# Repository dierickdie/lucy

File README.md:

# Lucy

An 4x12 ortho plus macro column keyboard.

**USE AT YOUR OWN RISK!!!** I am not responsible for any dumb things you do. Like fry your computer, break anything, etc.

## FAQ:
#### Does it have MIT/2x2u/etc.? 
No. Grid for life

#### Does it have backlighting?
No

#### Does it have RGB?
No

#### Does it have hotswap?
~No~ Fine

#### Does it have Alps support?
No

#### Choc support?
No

#### Encoder?
Not anymore; they're are a dead meme

#### Flex cuts?
See response to encoder

#### Will you add any of these?
No

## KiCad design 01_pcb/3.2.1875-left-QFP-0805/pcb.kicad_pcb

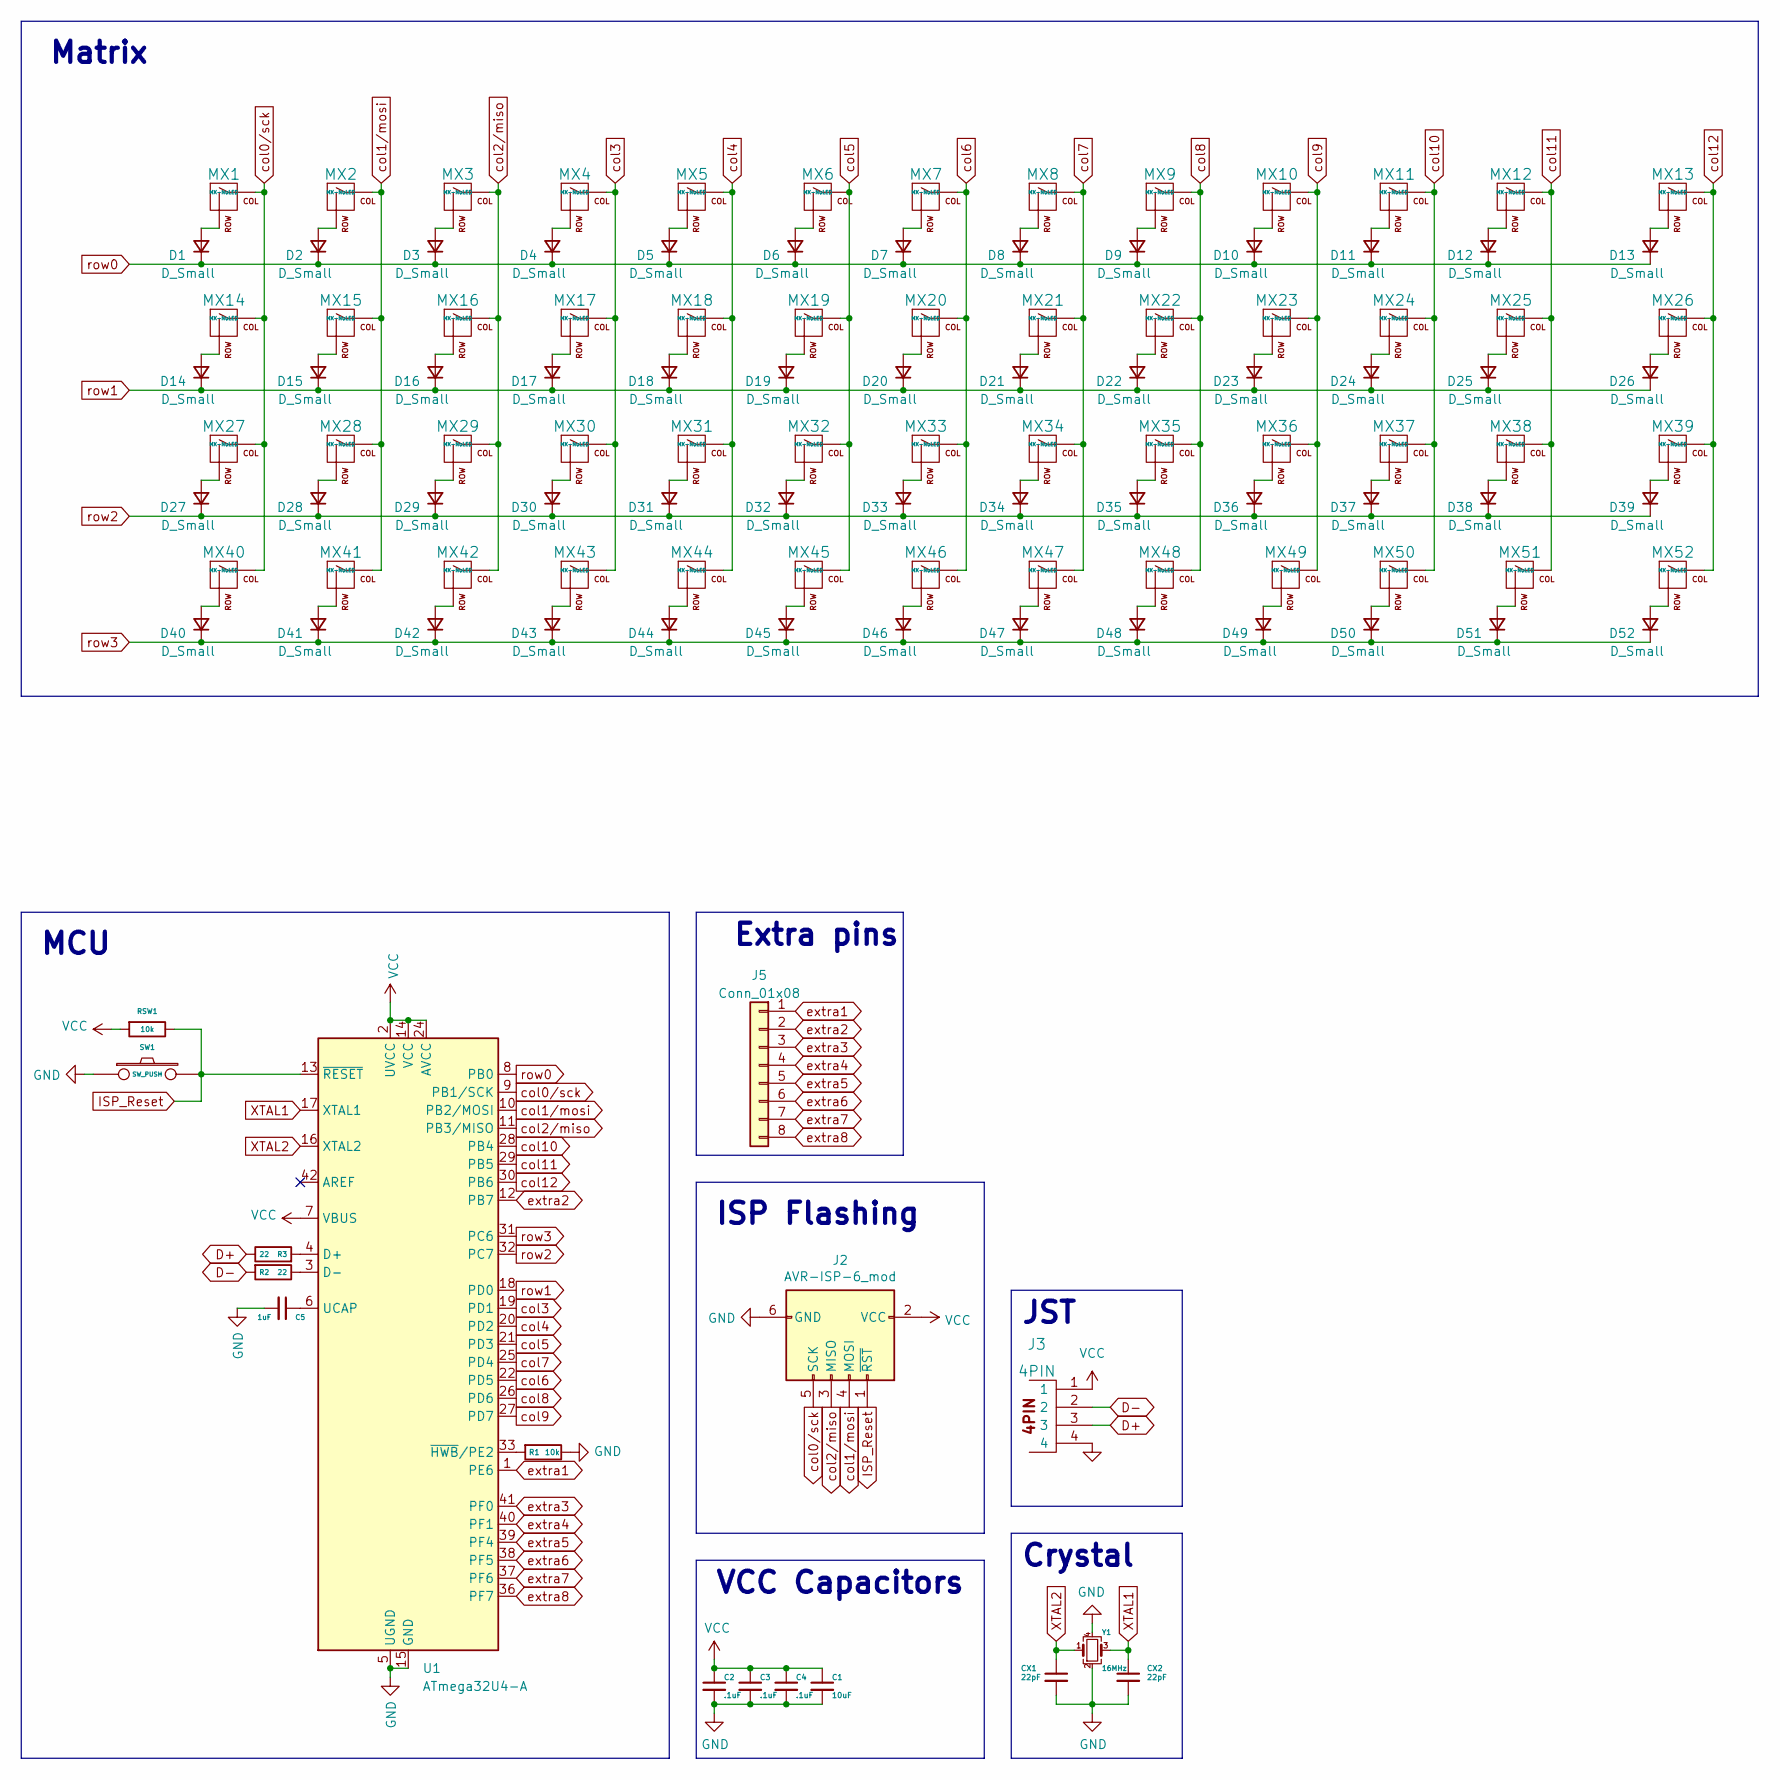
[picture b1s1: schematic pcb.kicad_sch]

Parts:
C1: 10uF; C_0805_2012Metric
C2, C3, C4: .1uF; C_0805_2012Metric
C5: 1uF; C_0805_2012Metric
CX1, CX2: 22pF; C_0805_2012Metric
D1, D2, D3, D4, D5, D6, D7, D8, D9, D10, D11, D12, D13, D14, D15, D16, D17, D18, D19, D20, D21, D22, D23, D24, D25, D26, D27, D28, D29, D30, D31, D32, D33, D34, D35, D36, D37, D38, D39, D40, D41, D42, D43, D44, D45, D46, D47, D48, D49, D50, D51, D52: D_Small; D_SOD-123
J2: AVR-ISP-6_mod; PinHeader_1x6_P2.54mm_Vertical
J3: 4PIN; JST_SH_SM04B-SRSS-TB_1x04-1MP_P1.00mm_Horizontal
J5: Conn_01x08; PinSocket_1x08_P2.54mm_Vertical
MX1, MX2, MX3, MX4, MX5, MX6, MX7, MX8, MX9, MX10, MX11, MX12, MX13, MX14, MX15, MX16, MX17, MX18, MX19, MX20, MX21, MX22, MX23, MX24, MX25, MX26, MX27, MX28, MX29, MX30, MX31, MX32, MX33, MX34, MX35, MX36, MX37, MX38, MX39, MX40, MX41, MX42, MX43, MX44, MX45, MX46, MX47, MX48, MX49, MX50, MX51, MX52: MX-NoLED; SW_MX_HS_S_1u
R1: 10k; R_0805_2012Metric
R2, R3: 22; R_0805_2012Metric
RSW1: 10k; R_0805_2012Metric
SW1: SW_PUSH; SKQG-1155865
U1: ATmega32U4-A; TQFP-44_10x10mm_P0.8mm
Y1: 16MHz; Crystal_SMD_3225-4Pin_3.2x2.5mm

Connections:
D+: J3.3, R3.1
D-: J3.2, R2.2
GND: C1.2, C2.2, C3.2, C4.2, C5.2, CX1.2, CX2.2, J2.6 (GND), J3.4, R1.1, SW1.1, U1.5 (UGND), U1.15 (GND), U1.23 (GND), U1.35 (GND), U1.43 (GND), Y1.2, Y1.4
ISP_Reset: J2.1 (~RST), RSW1.1, SW1.2, U1.13 (~RESET)
unnamed: D1.2 (A), MX1.2 (ROW)
unnamed: D2.2 (A), MX2.2 (ROW)
unnamed: D3.2 (A), MX3.2 (ROW)
unnamed: D4.2 (A), MX4.2 (ROW)
unnamed: D5.2 (A), MX5.2 (ROW)
unnamed: D6.2 (A), MX6.2 (ROW)
unnamed: D7.2 (A), MX7.2 (ROW)
unnamed: D8.2 (A), MX8.2 (ROW)
unnamed: D9.2 (A), MX9.2 (ROW)
unnamed: D10.2 (A), MX10.2 (ROW)
unnamed: D11.2 (A), MX11.2 (ROW)
unnamed: D12.2 (A), MX12.2 (ROW)
unnamed: D13.2 (A), MX13.2 (ROW)
unnamed: D14.2 (A), MX14.2 (ROW)
unnamed: D15.2 (A), MX15.2 (ROW)
unnamed: D16.2 (A), MX16.2 (ROW)
unnamed: D17.2 (A), MX17.2 (ROW)
unnamed: D18.2 (A), MX18.2 (ROW)
unnamed: D19.2 (A), MX19.2 (ROW)
unnamed: D20.2 (A), MX20.2 (ROW)
unnamed: D21.2 (A), MX21.2 (ROW)
unnamed: D22.2 (A), MX22.2 (ROW)
unnamed: D23.2 (A), MX23.2 (ROW)
unnamed: D24.2 (A), MX24.2 (ROW)
unnamed: D25.2 (A), MX25.2 (ROW)
unnamed: D26.2 (A), MX26.2 (ROW)
unnamed: D27.2 (A), MX27.2 (ROW)
unnamed: D28.2 (A), MX28.2 (ROW)
unnamed: D29.2 (A), MX29.2 (ROW)
unnamed: D30.2 (A), MX30.2 (ROW)
unnamed: D31.2 (A), MX31.2 (ROW)
unnamed: D32.2 (A), MX32.2 (ROW)
unnamed: D33.2 (A), MX33.2 (ROW)
unnamed: D34.2 (A), MX34.2 (ROW)
unnamed: D35.2 (A), MX35.2 (ROW)
unnamed: D36.2 (A), MX36.2 (ROW)
unnamed: D37.2 (A), MX37.2 (ROW)
unnamed: D38.2 (A), MX38.2 (ROW)
unnamed: D39.2 (A), MX39.2 (ROW)
unnamed: D40.2 (A), MX40.2 (ROW)
unnamed: D41.2 (A), MX41.2 (ROW)
unnamed: D42.2 (A), MX42.2 (ROW)
unnamed: D43.2 (A), MX43.2 (ROW)
unnamed: D44.2 (A), MX44.2 (ROW)
unnamed: D45.2 (A), MX45.2 (ROW)
unnamed: D46.2 (A), MX46.2 (ROW)
unnamed: D47.2 (A), MX47.2 (ROW)
unnamed: D48.2 (A), MX48.2 (ROW)
unnamed: D49.2 (A), MX49.2 (ROW)
unnamed: D50.2 (A), MX50.2 (ROW)
unnamed: D51.2 (A), MX51.2 (ROW)
unnamed: D52.2 (A), MX52.2 (ROW)
unnamed: R3.2, U1.4 (D+)
unnamed: R2.1, U1.3 (D-)
unnamed: C5.1, U1.6 (UCAP)
unnamed: R1.2, U1.33 (~HWB/PE2)
VCC: C1.1, C2.1, C3.1, C4.1, J2.2 (VCC), J3.1, RSW1.2, U1.2 (UVCC), U1.7 (VBUS), U1.14 (VCC), U1.24 (AVCC), U1.34 (VCC), U1.44 (AVCC)
XTAL1: CX2.1, U1.17 (XTAL1), Y1.3
XTAL2: CX1.1, U1.16 (XTAL2), Y1.1
col0/sck: J2.5 (SCK), MX1.1 (COL), MX14.1 (COL), MX27.1 (COL), MX40.1 (COL), U1.9 (PB1/SCK)
col1/mosi: J2.4 (MOSI), MX2.1 (COL), MX15.1 (COL), MX28.1 (COL), MX41.1 (COL), U1.10 (PB2/MOSI)
col2/miso: J2.3 (MISO), MX3.1 (COL), MX16.1 (COL), MX29.1 (COL), MX42.1 (COL), U1.11 (PB3/MISO)
col3: MX4.1 (COL), MX17.1 (COL), MX30.1 (COL), MX43.1 (COL), U1.19 (PD1)
col4: MX5.1 (COL), MX18.1 (COL), MX31.1 (COL), MX44.1 (COL), U1.20 (PD2)
col5: MX6.1 (COL), MX19.1 (COL), MX32.1 (COL), MX45.1 (COL), U1.21 (PD3)
col6: MX7.1 (COL), MX20.1 (COL), MX33.1 (COL), MX46.1 (COL), U1.22 (PD5)
col7: MX8.1 (COL), MX21.1 (COL), MX34.1 (COL), MX47.1 (COL), U1.25 (PD4)
col8: MX9.1 (COL), MX22.1 (COL), MX35.1 (COL), MX48.1 (COL), U1.26 (PD6)
col9: MX10.1 (COL), MX23.1 (COL), MX36.1 (COL), MX49.1 (COL), U1.27 (PD7)
col10: MX11.1 (COL), MX24.1 (COL), MX37.1 (COL), MX50.1 (COL), U1.28 (PB4)
col11: MX12.1 (COL), MX25.1 (COL), MX38.1 (COL), MX51.1 (COL), U1.29 (PB5)
col12: MX13.1 (COL), MX26.1 (COL), MX39.1 (COL), MX52.1 (COL), U1.30 (PB6)
extra1: J5.1, U1.1 (PE6)
extra2: J5.2, U1.12 (PB7)
extra3: J5.3, U1.41 (PF0)
extra4: J5.4, U1.40 (PF1)
extra5: J5.5, U1.39 (PF4)
extra6: J5.6, U1.38 (PF5)
extra7: J5.7, U1.37 (PF6)
extra8: J5.8, U1.36 (PF7)
row0: D1.1 (K), D2.1 (K), D3.1 (K), D4.1 (K), D5.1 (K), D6.1 (K), D7.1 (K), D8.1 (K), D9.1 (K), D10.1 (K), D11.1 (K), D12.1 (K), D13.1 (K), U1.8 (PB0)
row1: D14.1 (K), D15.1 (K), D16.1 (K), D17.1 (K), D18.1 (K), D19.1 (K), D20.1 (K), D21.1 (K), D22.1 (K), D23.1 (K), D24.1 (K), D25.1 (K), D26.1 (K), U1.18 (PD0)
row2: D27.1 (K), D28.1 (K), D29.1 (K), D30.1 (K), D31.1 (K), D32.1 (K), D33.1 (K), D34.1 (K), D35.1 (K), D36.1 (K), D37.1 (K), D38.1 (K), D39.1 (K), U1.32 (PC7)
row3: D40.1 (K), D41.1 (K), D42.1 (K), D43.1 (K), D44.1 (K), D45.1 (K), D46.1 (K), D47.1 (K), D48.1 (K), D49.1 (K), D50.1 (K), D51.1 (K), D52.1 (K), U1.31 (PC6)

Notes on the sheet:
ISP Flashing
Matrix
VCC Capacitors
Crystal
Extra pins
JST
MCU

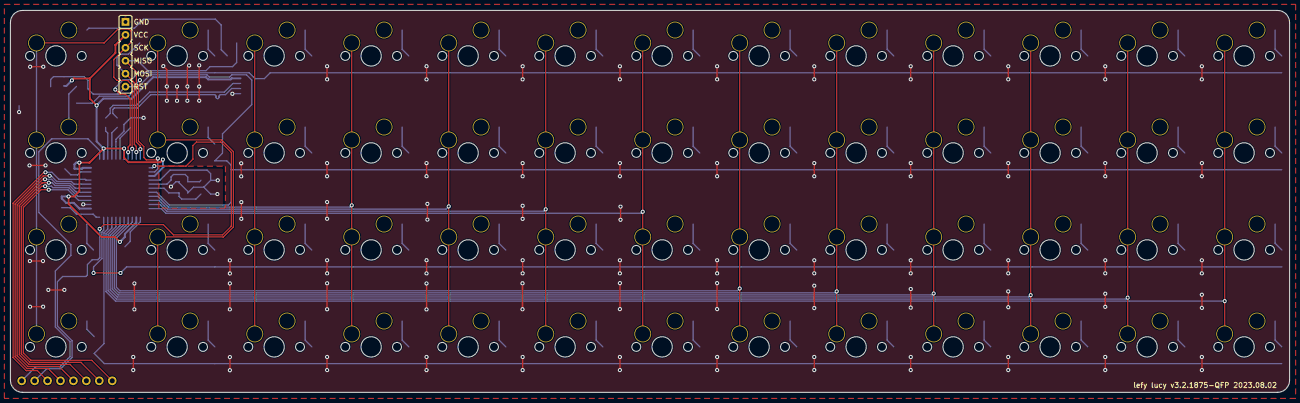
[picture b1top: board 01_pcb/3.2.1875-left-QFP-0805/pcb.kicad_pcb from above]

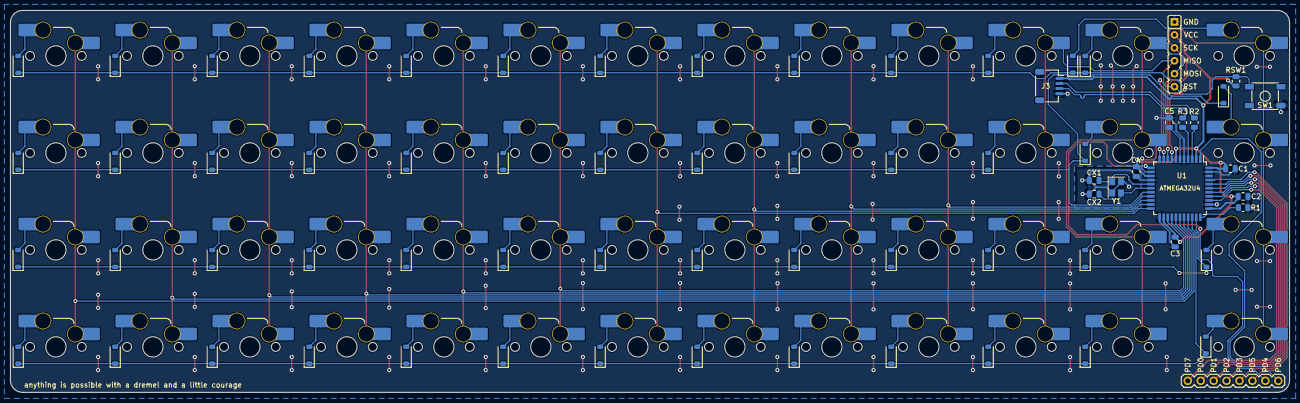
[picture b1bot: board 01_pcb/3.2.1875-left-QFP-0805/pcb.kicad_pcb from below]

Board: 2 copper layers, 251.2 x 75.0 mm, 121 parts (121 on the bottom side), 88 nets.

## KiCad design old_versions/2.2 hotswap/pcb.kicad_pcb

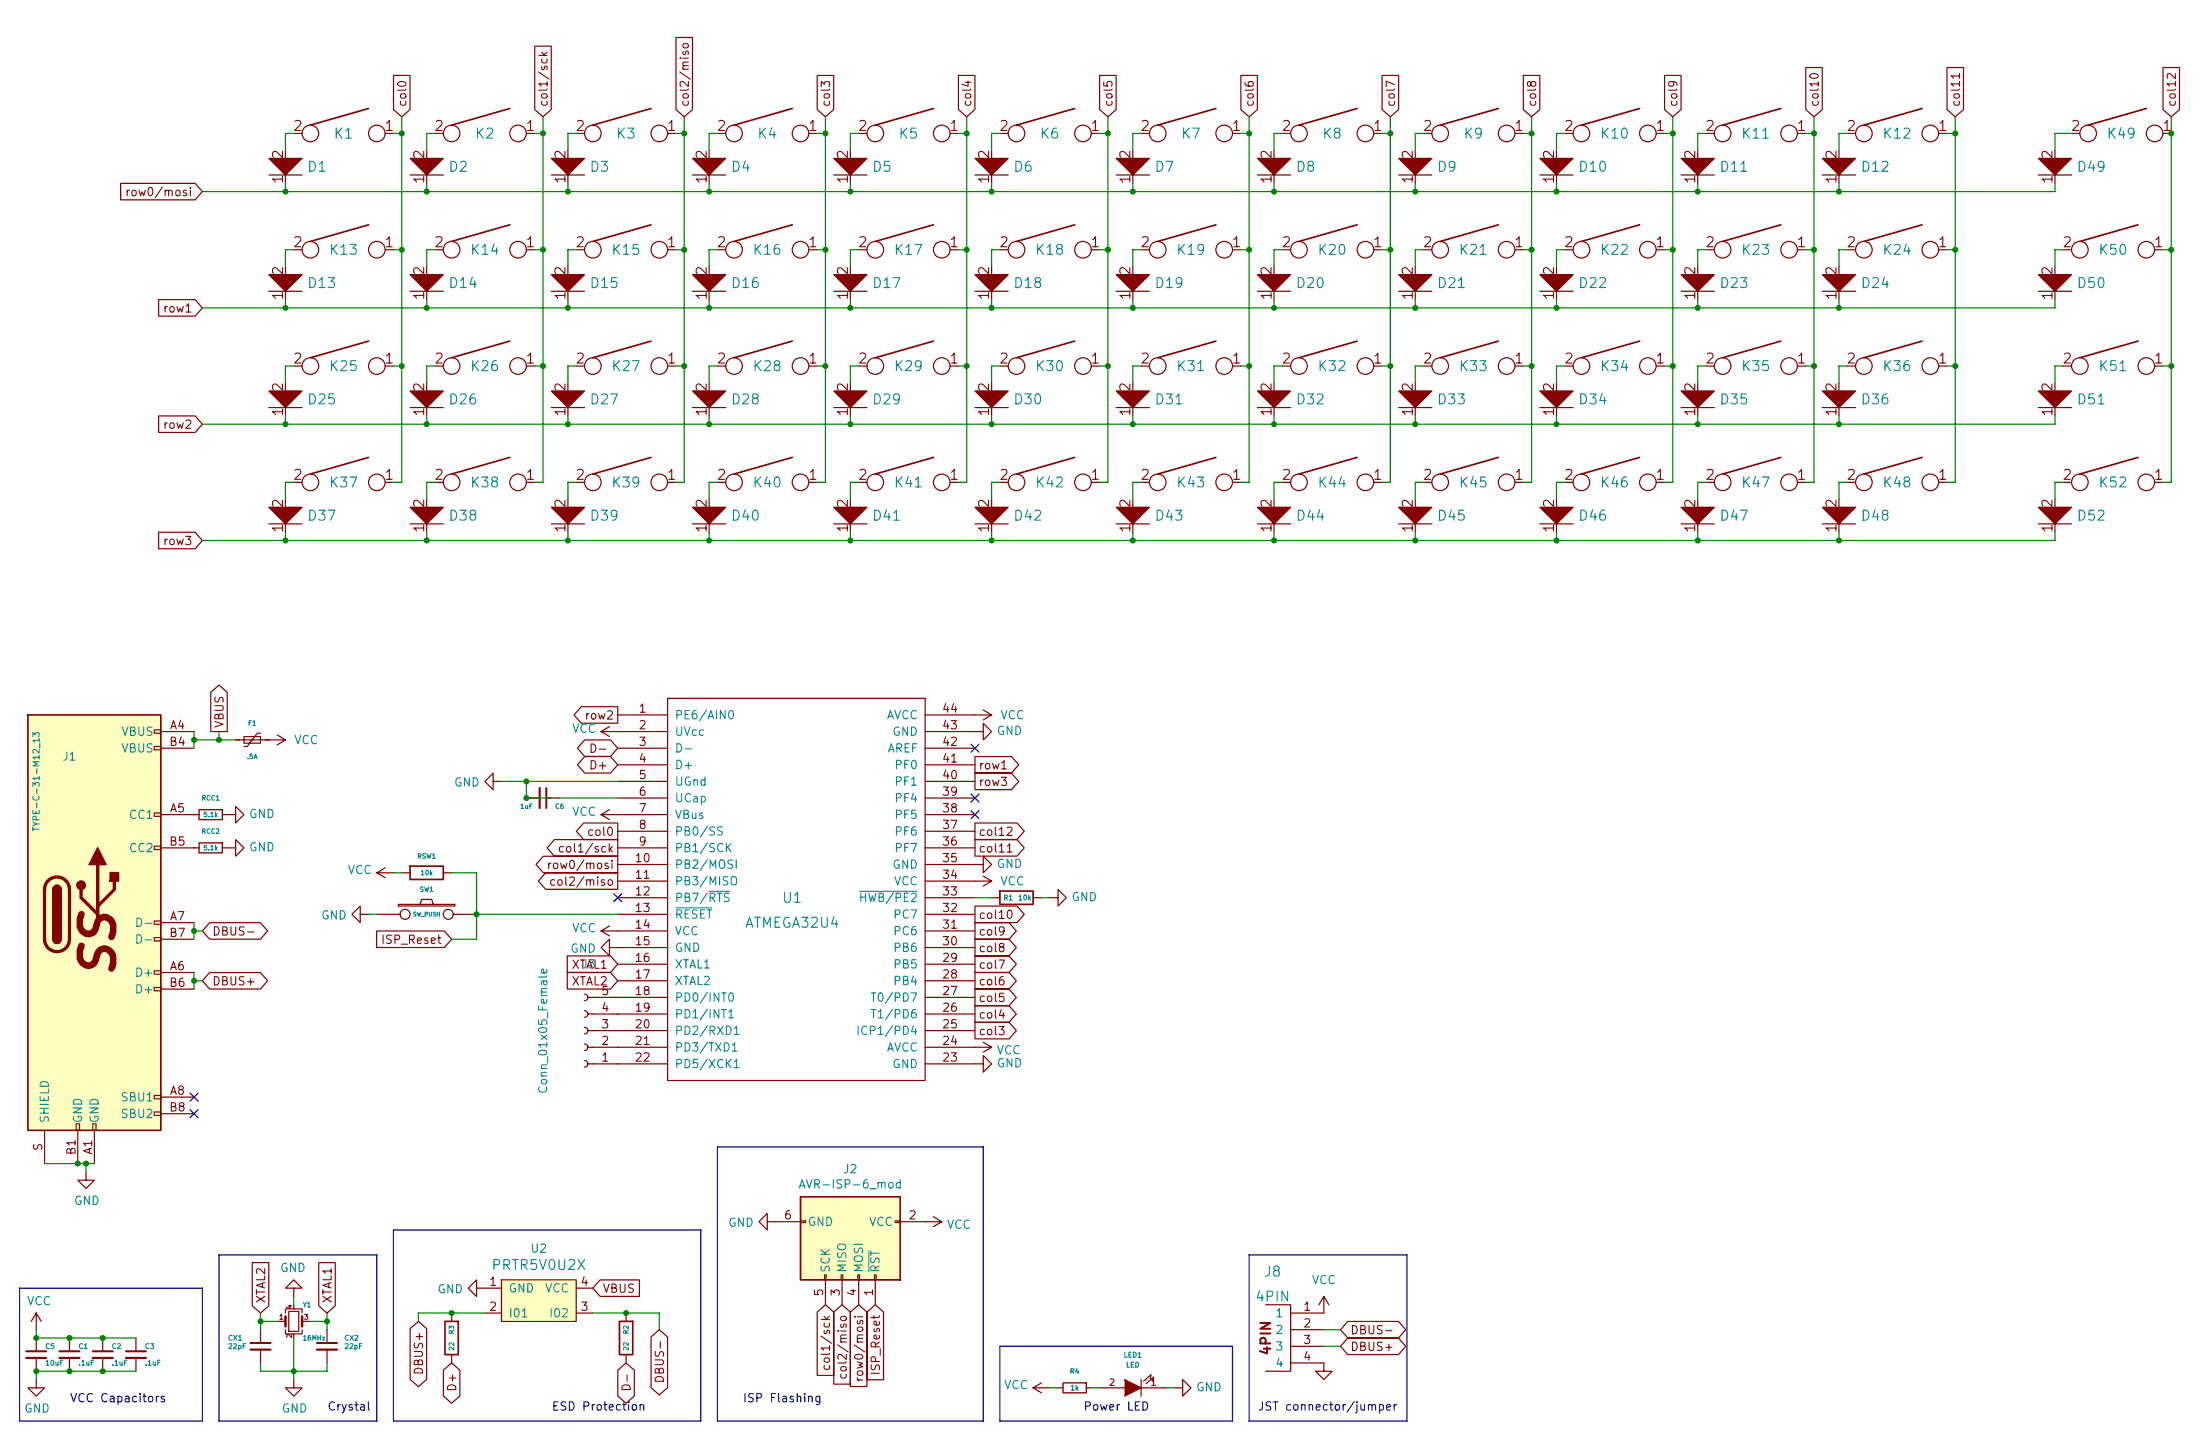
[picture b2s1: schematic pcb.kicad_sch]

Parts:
C1, C2, C3: .1uF; C_0805_2012Metric_Pad1.18x1.45mm_HandSolder
C5: 10uF; C_0805_2012Metric_Pad1.18x1.45mm_HandSolder
C6: 1uF; C_0805_2012Metric_Pad1.18x1.45mm_HandSolder
CX1, CX2: 22pF; C_0805_2012Metric_Pad1.18x1.45mm_HandSolder
D1, D2, D3, D4, D5, D6, D7, D8, D9, D10, D11, D12, D13, D14, D15, D16, D17, D18, D19, D20, D21, D22, D23, D24, D25, D26, D27, D28, D29, D30, D31, D32, D33, D34, D35, D36, D37, D38, D39, D40, D41, D42, D43, D44, D45, D46, D47, D48, D49, D50, D51, D52: D; D_SOD-123_modified
F1: .5A; Fuse_0805_2012Metric_Pad1.15x1.40mm_HandSolder
J1: TYPE-C-31-M12_13; TYPE-C-31-M-12
J2: AVR-ISP-6_mod; ICSP-Header_small_pins
J3: Conn_01x05_Female; PinHeader_1x05_P2.54mm_Vertical
J8: 4PIN; JST_SH_SM04B-SRSS-TB_1x04-1MP_P1.00mm_Horizontal
K1, K2, K3, K4, K5, K6, K7, K8, K9, K10, K11, K12, K13, K14, K15, K16, K17, K18, K19, K20, K21, K22, K23, K24, K25, K26, K27, K28, K29, K30, K31, K32, K33, K34, K35, K36, K37, K38, K39, K40, K41, K42, K43, K44, K45, K46, K47, K48, K49, K50, K51, K52: KEYSW; MXOnly-1U-Hotswap
LED1: LED; LED_0805_2012Metric_Pad1.15x1.40mm_HandSolder
R1: 10k; R_0805_2012Metric_Pad1.20x1.40mm_HandSolder
R2, R3: 22; R_0805_2012Metric_Pad1.20x1.40mm_HandSolder
R4: 1k; R_0805_2012Metric_Pad1.20x1.40mm_HandSolder
RCC1, RCC2: 5.1k; R_0805_2012Metric_Pad1.20x1.40mm_HandSolder
RSW1: 10k; R_0805_2012Metric_Pad1.20x1.40mm_HandSolder
SW1: SW_PUSH; SKQG-1155865
U1: ATMEGA32U4; ATMEGA32U4-AU
U2: PRTR5V0U2X; SOT-143B
Y1: 16MHz; Crystal_SMD_3225-4Pin_3.2x2.5mm_HandSoldering

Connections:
D+: R3.1, U1.4 (D+)
D-: R2.1, U1.3 (D-)
DBUS+: J1.A6 (D+), J1.B6 (D+), J8.3, R3.2, U2.2 (I01)
DBUS-: J1.A7 (D-), J1.B7 (D-), J8.2, R2.2, U2.3 (I02)
GND: C1.2, C2.2, C3.2, C5.2, C6.2, CX1.2, CX2.2, J1.A1 (GND), J1.B1 (GND), J1.S (SHIELD), J2.6 (GND), J8.4, LED1.1 (K), R1.1, RCC1.1, RCC2.1, SW1.1, U1.5 (UGnd), U1.15 (GND), U1.23 (GND), U1.35 (GND), U1.43 (GND), U2.1 (GND), Y1.2, Y1.4
ISP_Reset: J2.1 (~RST), RSW1.1, SW1.2, U1.13 (~RESET)
unnamed: D1.2, K1.2
unnamed: D2.2, K2.2
unnamed: D3.2, K3.2
unnamed: D4.2, K4.2
unnamed: D5.2, K5.2
unnamed: D6.2, K6.2
unnamed: D7.2, K7.2
unnamed: D8.2, K8.2
unnamed: D9.2, K9.2
unnamed: D10.2, K10.2
unnamed 16: D11.2, K11.2; also elsewhere on the board
unnamed: D12.2, K12.2
unnamed: D13.2, K13.2
unnamed: D14.2, K14.2
unnamed: D15.2, K15.2
unnamed: D16.2, K16.2
unnamed: D17.2, K17.2
unnamed: D18.2, K18.2
unnamed: D19.2, K19.2
unnamed: D20.2, K20.2
unnamed: D21.2, K21.2
unnamed 27: D22.2, K22.2; also elsewhere on the board
unnamed: D23.2, K23.2
unnamed: D24.2, K24.2
unnamed: D25.2, K25.2
unnamed: D26.2, K26.2
unnamed: D27.2, K27.2
unnamed: D28.2, K28.2
unnamed: D29.2, K29.2
unnamed: D30.2, K30.2
unnamed: D31.2, K31.2
unnamed: D32.2, K32.2
unnamed: D33.2, K33.2
unnamed: D34.2, K34.2
unnamed 40: D35.2, K35.2; also elsewhere on the board
unnamed: D36.2, K36.2
unnamed: D37.2, K37.2
unnamed: D38.2, K38.2
unnamed: D39.2, K39.2
unnamed 45: D40.2, K40.2; also elsewhere on the board
unnamed 46: D41.2, K41.2; also elsewhere on the board
unnamed: D42.2, K42.2
unnamed: D43.2, K43.2
unnamed: D44.2, K44.2
unnamed: D45.2, K45.2
unnamed: D46.2, K46.2
unnamed: D47.2, K47.2
unnamed: D48.2, K48.2
unnamed: D49.2, K49.2
unnamed: D50.2, K50.2
unnamed: D51.2, K51.2
unnamed: D52.2, K52.2
unnamed: J1.A5 (CC1), RCC1.2
unnamed: J1.B5 (CC2), RCC2.2
unnamed: J3.1, U1.22 (PD5/XCK1)
unnamed: J3.2, U1.21 (PD3/TXD1)
unnamed: J3.3, U1.20 (PD2/RXD1)
unnamed: J3.4, U1.19 (PD1/INT1)
unnamed: J3.5, U1.18 (PD0/INT0)
unnamed: LED1.2 (A), R4.1
unnamed: C6.1, U1.6 (UCap)
unnamed: R1.2, U1.33 (~HWB/PE2)
VBUS: F1.2, J1.A4 (VBUS), J1.B4 (VBUS), U2.4 (VCC)
VCC: C1.1, C2.1, C3.1, C5.1, F1.1, J2.2 (VCC), J8.1, R4.2, RSW1.2, U1.2 (UVcc), U1.7 (VBus), U1.14 (VCC), U1.24 (AVCC), U1.34 (VCC), U1.44 (AVCC)
col0: K1.1, K13.1, K25.1, K37.1, U1.8 (PB0/SS)
col1/sck: J2.5 (SCK), K2.1, K14.1, K26.1, K38.1, U1.9 (PB1/SCK)
col2/miso: J2.3 (MISO), K3.1, K15.1, K27.1, K39.1, U1.11 (PB3/MISO)
col3: K4.1, K16.1, K28.1, K40.1, U1.25 (ICP1/PD4); also elsewhere on the board
col4: K5.1, K17.1, K29.1, K41.1, U1.26 (T1/PD6); also elsewhere on the board
col5: K6.1, K18.1, K30.1, K42.1, U1.27 (T0/PD7)
col6: K7.1, K19.1, K31.1, K43.1, U1.28 (PB4)
col7: K8.1, K20.1, K32.1, K44.1, U1.29 (PB5)
col8: K9.1, K21.1, K33.1, K45.1, U1.30 (PB6)
col9: K10.1, K22.1, K34.1, K46.1, U1.31 (PC6); also elsewhere on the board
col10: K11.1, K23.1, K35.1, K47.1, U1.32 (PC7); also elsewhere on the board
col11: K12.1, K24.1, K36.1, K48.1, U1.36 (PF7)
col12: K49.1, K50.1, K51.1, K52.1, U1.37 (PF6)
row0/mosi: D1.1, D2.1, D3.1, D4.1, D5.1, D6.1, D7.1, D8.1, D9.1, D10.1, D11.1, D12.1, D49.1, J2.4 (MOSI), U1.10 (PB2/MOSI)
row1: D13.1, D14.1, D15.1, D16.1, D17.1, D18.1, D19.1, D20.1, D21.1, D22.1, D23.1, D24.1, D50.1, U1.41 (PF0)
row2: D25.1, D26.1, D27.1, D28.1, D29.1, D30.1, D31.1, D32.1, D33.1, D34.1, D35.1, D36.1, D51.1, U1.1 (PE6/AIN0)
row3: D37.1, D38.1, D39.1, D40.1, D41.1, D42.1, D43.1, D44.1, D45.1, D46.1, D47.1, D48.1, D52.1, U1.40 (PF1)

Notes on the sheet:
ESD Protection
JST connector/jumper
Crystal
Power LED
VCC Capacitors
ISP Flashing

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
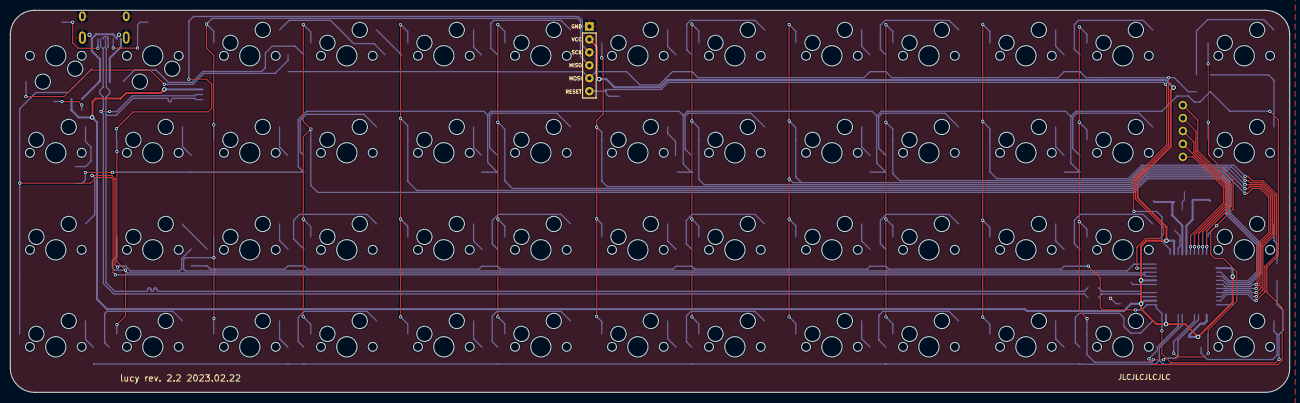
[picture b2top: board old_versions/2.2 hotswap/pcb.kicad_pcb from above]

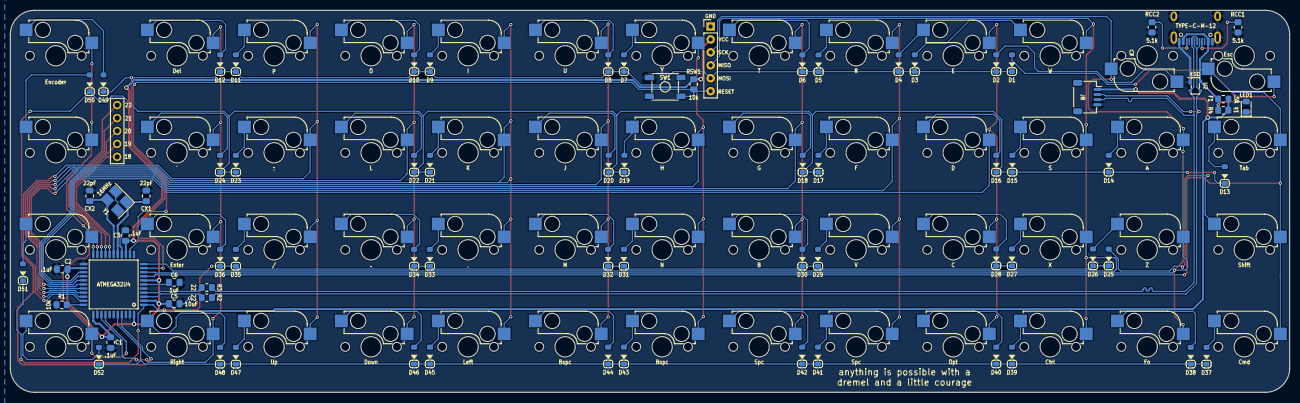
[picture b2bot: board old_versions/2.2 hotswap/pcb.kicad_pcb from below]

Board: 2 copper layers, 251.2 x 75.0 mm, 128 parts (76 on the bottom side), 89 nets.

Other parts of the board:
locked: KEYSW; MXOnly-1U-Hotswap
locked#2, locked#3, locked#4, locked#5: KEYSW; MXOnly-1U-Hotswap

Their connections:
unnamed 16: locked.2; also elsewhere on the board
unnamed 27: locked#5.2; also elsewhere on the board
unnamed 40: locked#4.2; also elsewhere on the board
unnamed 45: locked#2.2; also elsewhere on the board
unnamed 46: locked#3.2; also elsewhere on the board
col3: locked#2.1; also elsewhere on the board
col4: locked#3.1; also elsewhere on the board
col9: locked#5.1; also elsewhere on the board
col10: locked.1, locked#4.1; also elsewhere on the board

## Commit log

2020-07-23 Add gerbers
2020-07-25 Added ESD/shield protection
2020-07-25 Add keymaps
2020-07-26 .DS_Store banished!
2020-07-26 Routing data lines as differential pair
2020-07-26 Forgot to save schematic prior to last push
2020-08-03 Routed main VCC power trhough 10uF cap
2021-04-15 Create south facing LED PCB
2021-04-16 Rename Ori.c to ori.c
2021-04-16 Rename Ori.h to ori.h
2021-04-16 remove a column
2021-04-16 playing with tap dance
2021-04-25 routing tomfoolery
2021-04-25 final touches
2021-04-26 update
    added macro column to top plate
    re-routed some traces
    new previews
    removed some ground plane
2021-05-08 Moved macro column a tiny bit
2021-05-09 nada
2021-06-04 update rotary encoder functions
2021-07-12 19.05mm spacing; move macro column to right side
2021-08-07 updated plate holes
2021-08-14 Updated firmware
2021-08-18 added different plate mounts
2021-08-19 modify top plate
2021-08-21 add different top plates
2021-08-22 add non break off column
2021-08-31 update column names
2021-09-03 moved mounting holes
2021-09-09 remove snap off version
2021-09-09 remove 19mm version
2021-09-09 remove standoff cutouts
2021-09-09 move bottom mounting points and update previews
2021-09-09 update gerbers
2021-09-26 start new version
2021-09-26 new ESD protection
2021-09-26 update rev silkscreen
2021-09-30 re-enabled mousekeys in keymap; moved 1.1 to old versions
2021-10-03 re-route VCC lines
2021-10-03 add lucy text
2021-10-03 replace ori references to lucy
2021-10-03 new gerbers with new name
2021-10-03 rerouting
2021-10-07 Complete re-routing
2021-10-08 minor re-routing
2021-10-09 add v1.2 - sent to JLC
2021-10-17 rename files
2021-10-20 moved AREF pin to pin 1
2021-10-24 create slots for top plate
2021-10-24 update bottom plate
2021-10-24 Update fp-info-cache
2021-11-03 update plates
2021-11-30 new plates
2022-01-03 add hotswap
2022-01-19 added HS pcb, new plate design
2022-01-19 updated top plate
2022-01-24 3d files
2022-02-11 update 3d files
2022-02-11 kicad backups
2022-02-11 kicad backup
2022-02-11 tweak pcb
2022-03-10 summary
2022-03-14 Update keymap.c
    update macros
2022-03-14 new mounting points
2022-03-21 Create hotswap PCB with all south facing switches
2022-03-21 update pcb
2022-03-21 remove old plates
2022-03-21 rename plate files
2022-03-24 removed switch opening slots
2022-03-24 nearly ready to send PCB to manu
2022-03-28 making HS pcb flexy
2022-03-28 some preliminary 3d files
2022-03-28 flex hs psb
2022-03-28 backups
2022-03-28 finished routing
2022-03-29 route lines away from crystal
2022-03-29 remove temporary 3d files
2022-03-29 add mounting support for encoder
2022-04-11 pull old solder pcb
    current solder PCB was freezing in Kicad, pulled an old one and made changes. mostly just moved USB port up
2022-04-11 remove old hotswap pcb
    remove hotswap pcb with north facing switches
2022-04-11 rename flex hotswap pcb
2022-04-18 added gasket mounting to plate
2022-04-18 update HS pcb; sent to manu
2022-04-18 add gasket to plate
2022-04-18 remove bottom fr4 pate
2022-04-18 update firmware
2022-04-18 remove step files
2022-04-19 updated plate for gasket
2022-04-20 add hs flex gerbers
2022-04-20 flex plate
2022-04-20 add flex plate gerbers
2022-04-20 add flex plate files
2022-04-20 remove old backups
2022-04-20 plate gerbers
2022-04-20 archive v1.0 HS
    sorry github
2022-04-20 archive v1.0 HS flex
2022-04-20 update plate files
2022-04-27 update flex plate - changed to version A
2022-04-27 create flex plate ver. B
2022-06-05 hotswap breakaway
2022-06-05 updated solder pcb files
2022-06-05 kicad generated backups
2022-06-05 remove old versions that weren't submitted
2022-06-05 update firmware
    added magicboot
2022-06-05 updated plate designs
    add gasket mounting, replaced slots with holes for top mount
2022-06-05 remove old solder files
2022-06-05 flexy hotswap
2022-06-05 hotswap without flex cuts
2022-06-11 Remove breakaway PCB
2022-06-11 Remove old hotswap PCB without flex cuts
2022-06-11 Remove old Plate A
2022-06-11 updated gerbers
2022-06-11 remove old keymap files
2022-06-11 include 1.9 and 2.0 pcbs
2022-06-11 Sent to manu!
2022-06-11 rename folder
2022-06-16 reduced tab distance
2022-07-07 move notch to center
2022-07-07 updated gerber
2022-07-07 remove plating around switches
2022-08-31 Create right macro Lucy
2022-08-31 changed name to Lucy left macro
2022-08-31 update Plate A to include support for right macro
2022-08-31 changed name to left macro
2022-08-31 old versions
2022-08-31 Plate B updates
2022-08-31 iCloud files?
2022-08-31 remove old files
2022-08-31 moved mounting hole
2022-08-31 moved mounting hle
2022-08-31 renamed folder
2022-09-07 new gerbers
2022-09-11 removed bottom cutout for flex
    new case design doesn't need it
2023-01-25 remove flex cuts and encoder
2023-01-25 remove flex cuts, move mounting points
2023-01-25 updated schematic
2023-02-06 add 3d models to kicad footprints
2023-02-23 recessed USB port
    moved the usb port back a lot to make the case easier when using UDB
2023-02-23 ¯\_(ツ)_/¯
2023-03-27 moved USB port data line resistors
    also added 3d models, etc.
2023-03-27 update .gitignore to exclude backups
2023-03-27 ATMEGA32U4-MU
2023-03-27 begin clean board
2023-03-31 added ATMEGA-MU MCU
2023-03-31 all new routing for -MU MCU. v3.0
2023-03-31 remove stiffer plate
2023-03-31 replace plate files
2023-03-31 rename folders
2023-03-31 update plate and add gerbers for FR4
2023-03-31 move files
2023-03-31 add stitching vias
2023-04-01 add marbast library
2023-04-01 replaced SRV05-4 footprint
2023-04-12 add hand solderable pcb
2023-04-12 added text
2023-04-23 replace mx footprint with marbast footprints
2023-04-23 move folders
2023-04-28 remove usb - only daughterboard now
2023-05-10 final JLC production
2023-05-16 sent to JLC
2023-05-19 fixed macro gap
    stupid me had a 3/8" gap, and should have been 3/16" (0.25u vs 0.5u)
2023-05-19 updated QFN, removed some vias
2023-05-25 add KLE
2023-05-25 update names
2023-05-26 remove diode references
2023-07-08 moved JST connector 20mm
2023-08-09 .375in macro gap lefty lucy
2023-08-09 0.1875in macro gap lefty lucy
2023-08-09 lefty lucy firmware
2023-08-09 update .1875 PCB
2023-08-09 update footprints
2023-10-05 pcb updates
2024-12-09 update firmware to comply with new QMK
